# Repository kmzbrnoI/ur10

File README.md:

Universal relay module UR-10
============================

Module with 1 relay.

Designed in KiCad 9 by Jan Malina.

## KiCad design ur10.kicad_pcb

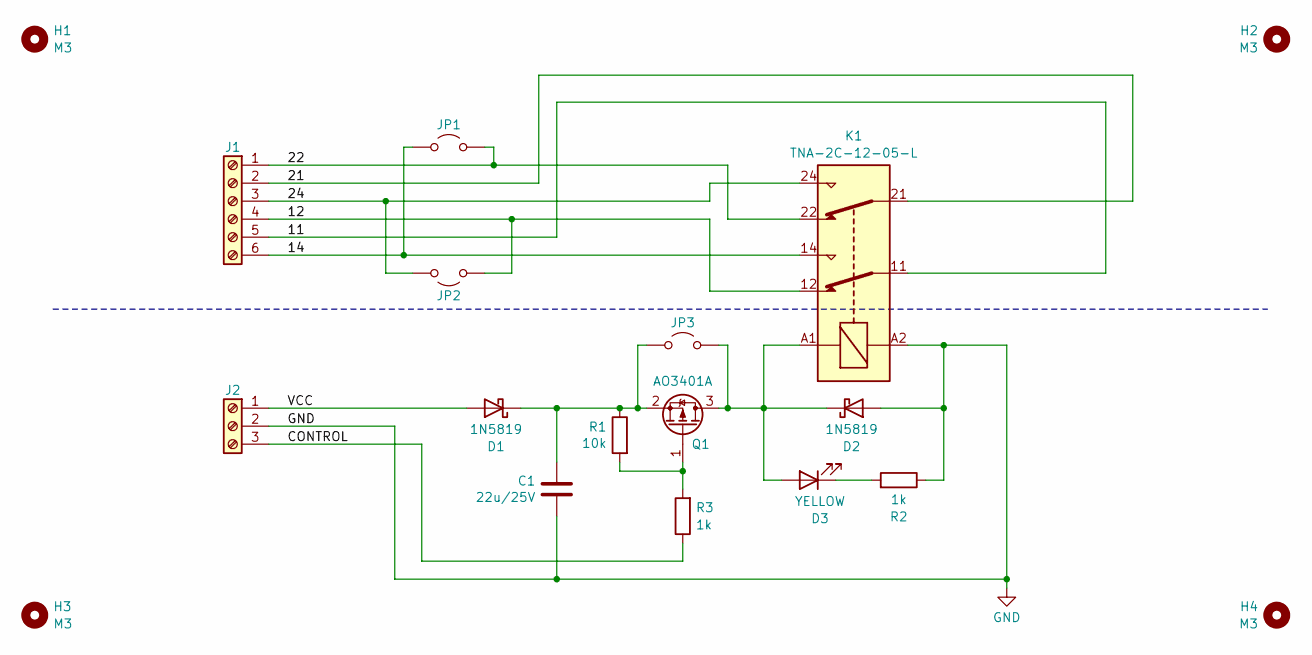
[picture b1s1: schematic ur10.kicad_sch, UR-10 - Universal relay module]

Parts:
C1: 22u/25V; C_0805_2012Metric_Pad1.18x1.45mm_HandSolder; LCSC C45783
D1, D2: 1N5819; D_SOD-123
D3: YELLOW; LED_0805_2012Metric_Pad1.15x1.40mm_HandSolder
H1, H2, H3, H4: M3; MountingHole_3.2mm_M3_Pad_Via
J1: MVE252-5-V-3x
J2: TerminalBlock_4Ucon_1x03_P3.50mm_Horizontal
JP1, JP2, JP3: PinHeader_1x02_P2.54mm_Vertical
K1: TNA-2C-12-05-L; Relay_DPDT_Schrack-RT2-FormC_RM5mm
Q1: AO3401A; SOT-23_Handsoldering
R1: 10k; R_0805_2012Metric_Pad1.20x1.40mm_HandSolder; LCSC C17414
R2, R3: 1k; R_0805_2012Metric_Pad1.20x1.40mm_HandSolder; LCSC C17513

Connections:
/11: J1.5, K1.11
/12: J1.4, JP2.2 (B), K1.12
/14: J1.6, JP1.1 (A), K1.14
/21: J1.2, K1.21
/22: J1.1, JP1.2 (B), K1.22
/24: J1.3, JP2.1 (A), K1.24
/CONTROL: J2.3, R3.1
/VCC: D1.2 (A), J2.1
GND: C1.2, D2.2 (A), J2.2, K1.A2, R2.1
unnamed: C1.1, D1.1 (K), JP3.1 (A), Q1.2 (S), R1.1
unnamed: D2.1 (K), D3.2 (A), JP3.2 (B), K1.A1, Q1.3 (D)
unnamed: D3.1 (K), R2.2
unnamed: Q1.1 (G), R1.2, R3.2

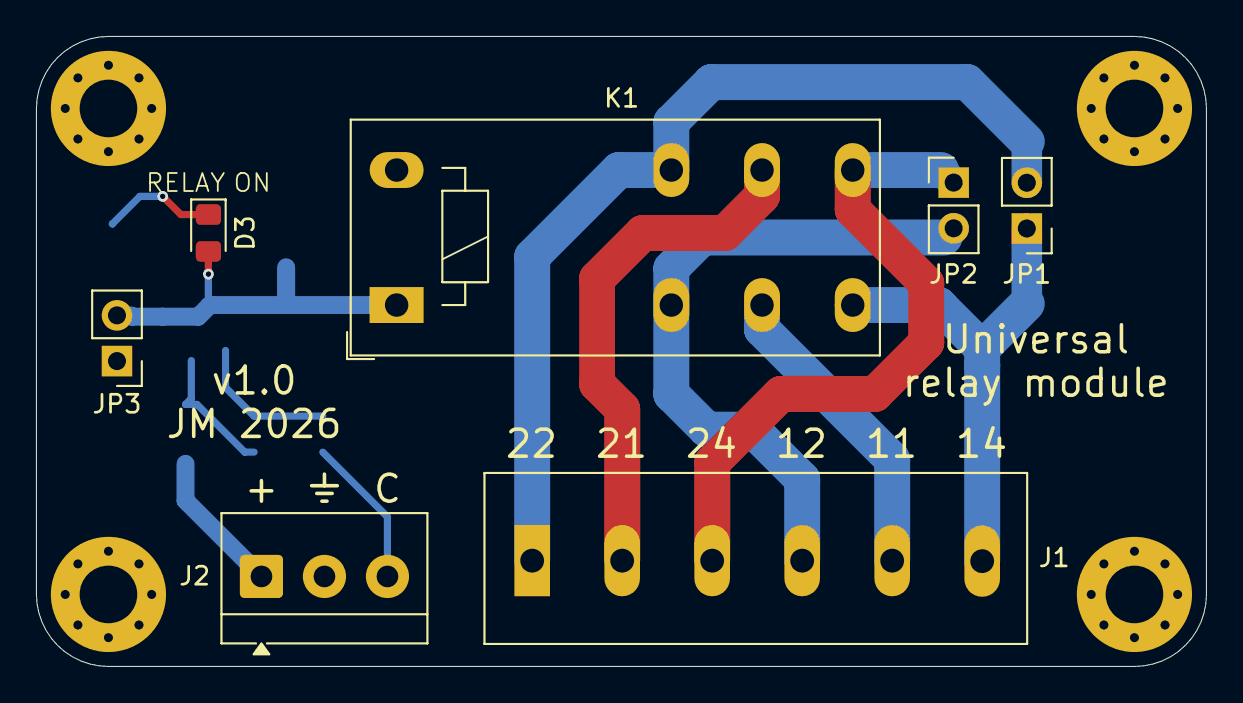
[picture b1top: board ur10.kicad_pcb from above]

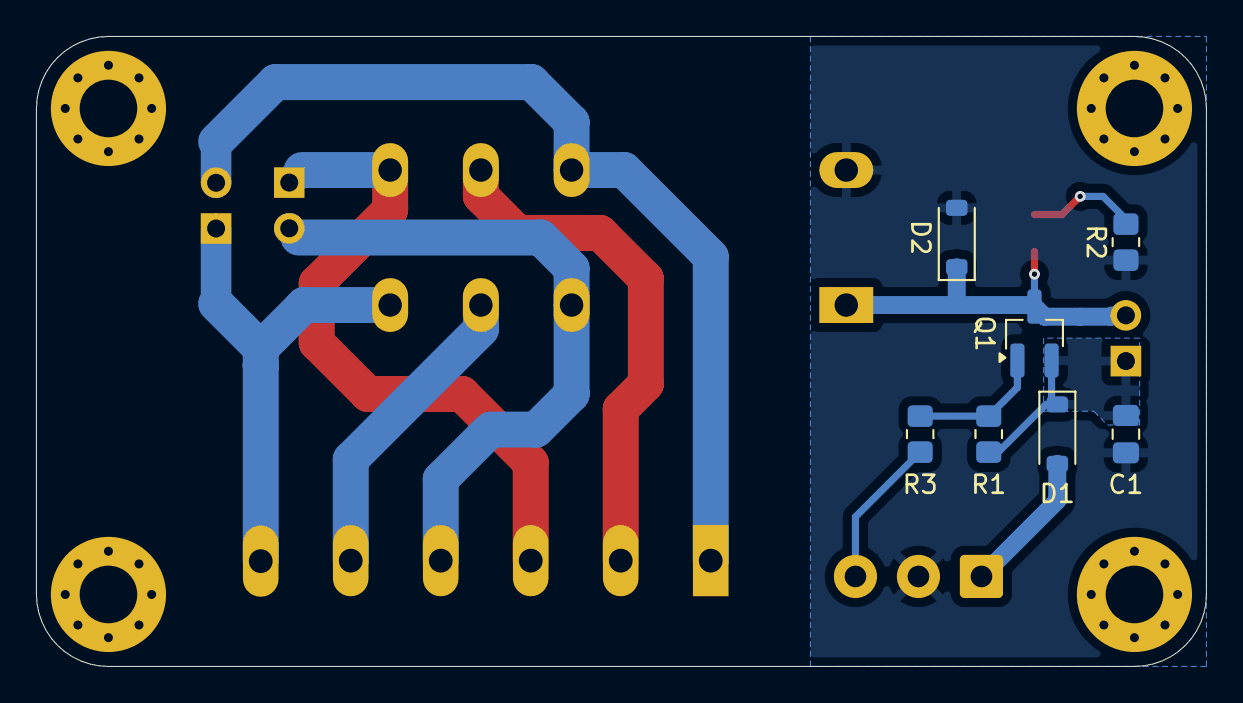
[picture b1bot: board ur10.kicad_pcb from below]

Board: 2 copper layers, 65.0 x 35.0 mm, 18 parts (7 on the bottom side), 13 nets.

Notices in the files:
ur10.kicad_sch:
https://creativecommons.org/licenses/by-sa/4.0
Released under the Creative Commons Attribution-ShareAlike 4.0 License
